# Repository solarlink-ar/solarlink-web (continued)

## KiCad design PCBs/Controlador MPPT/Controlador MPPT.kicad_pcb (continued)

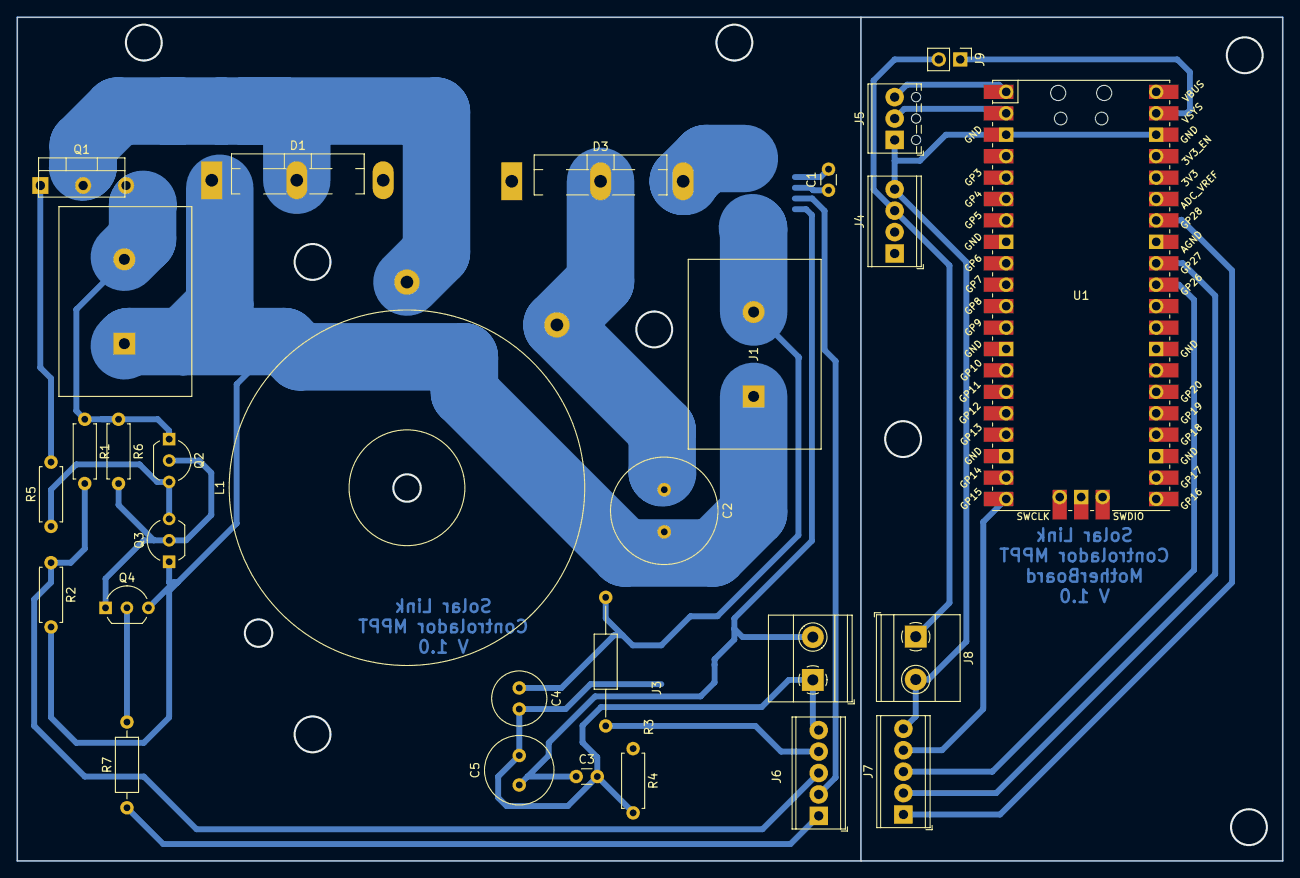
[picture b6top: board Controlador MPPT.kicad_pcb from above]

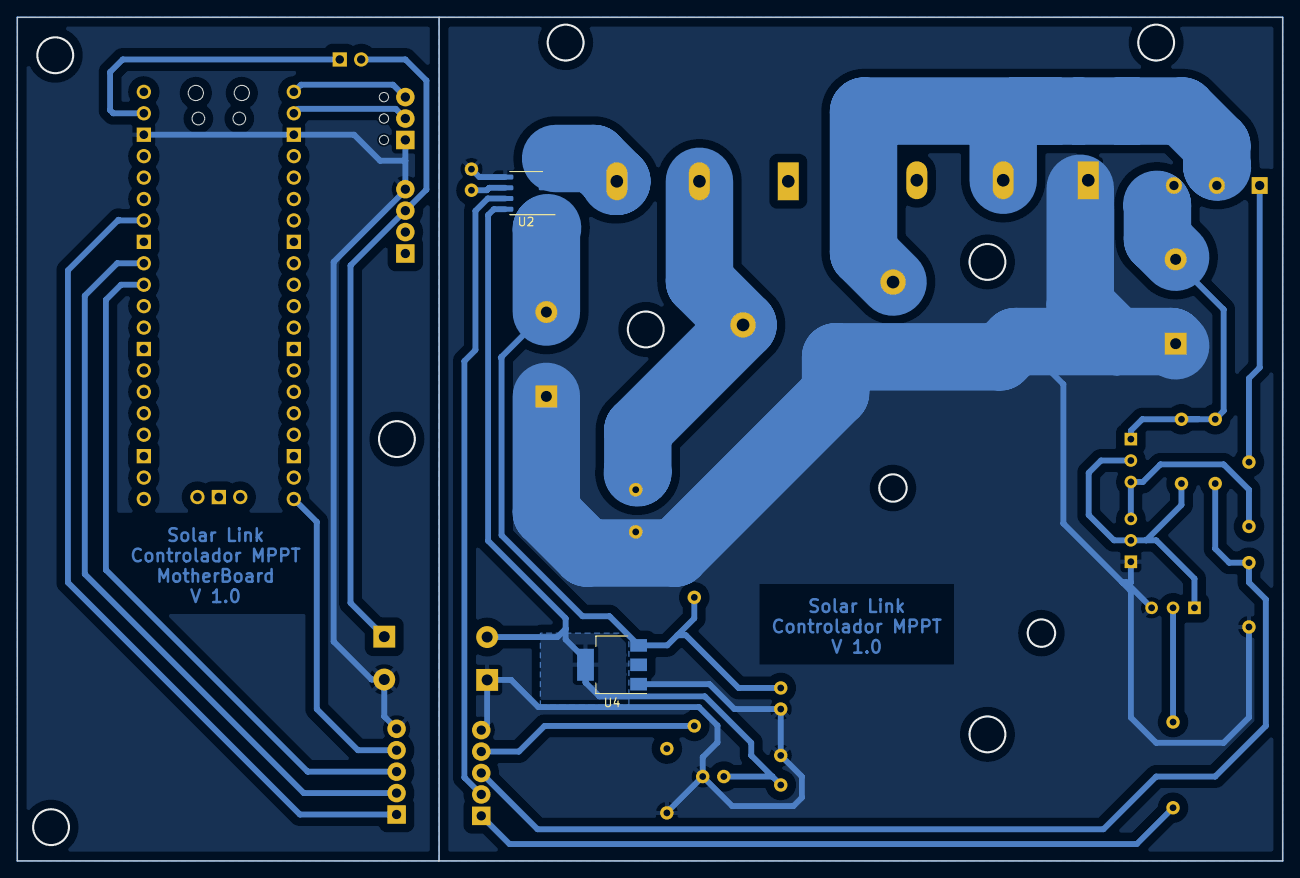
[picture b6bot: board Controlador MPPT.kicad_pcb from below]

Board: 2 copper layers, 150.0 x 100.0 mm, 31 parts (2 on the bottom side), 19 nets.

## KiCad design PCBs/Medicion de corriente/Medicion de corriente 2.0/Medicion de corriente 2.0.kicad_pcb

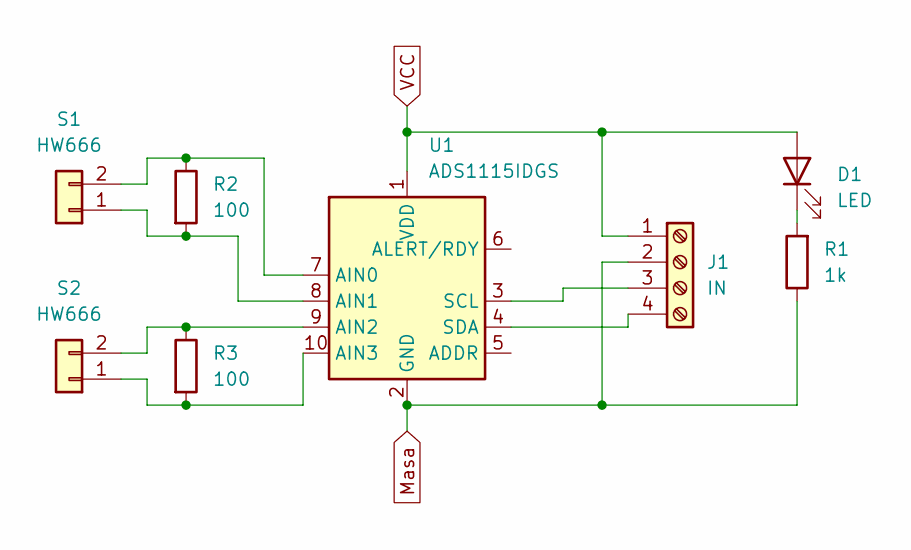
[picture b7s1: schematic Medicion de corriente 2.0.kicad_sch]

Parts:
D1: LED; LED_D3.0mm
J1: IN; TerminalBlock_Phoenix_MPT-0,5-4-2.54_1x04_P2.54mm_Horizontal
R1: 1k; R_Axial_DIN0207_L6.3mm_D2.5mm_P7.62mm_Horizontal
R2, R3: 100; R_Axial_DIN0207_L6.3mm_D2.5mm_P7.62mm_Horizontal
S1, S2: HW666; PinHeader_1x02_P2.54mm_Vertical
U1: ADS1115IDGS; PinHeader_1x10_P2.54mm_Vertical

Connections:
Masa: J1.2, R1.1, U1.2 (GND)
unnamed: D1.1 (K), R1.2
unnamed: J1.3, U1.3 (SCL)
unnamed: J1.4, U1.4 (SDA)
unnamed: R2.2, S1.1, U1.8 (AIN1)
unnamed: R2.1, S1.2, U1.7 (AIN0)
unnamed: R3.2, S2.1, U1.10 (AIN3)
unnamed: R3.1, S2.2, U1.9 (AIN2)
VCC: D1.2 (A), J1.1, U1.1 (VDD)

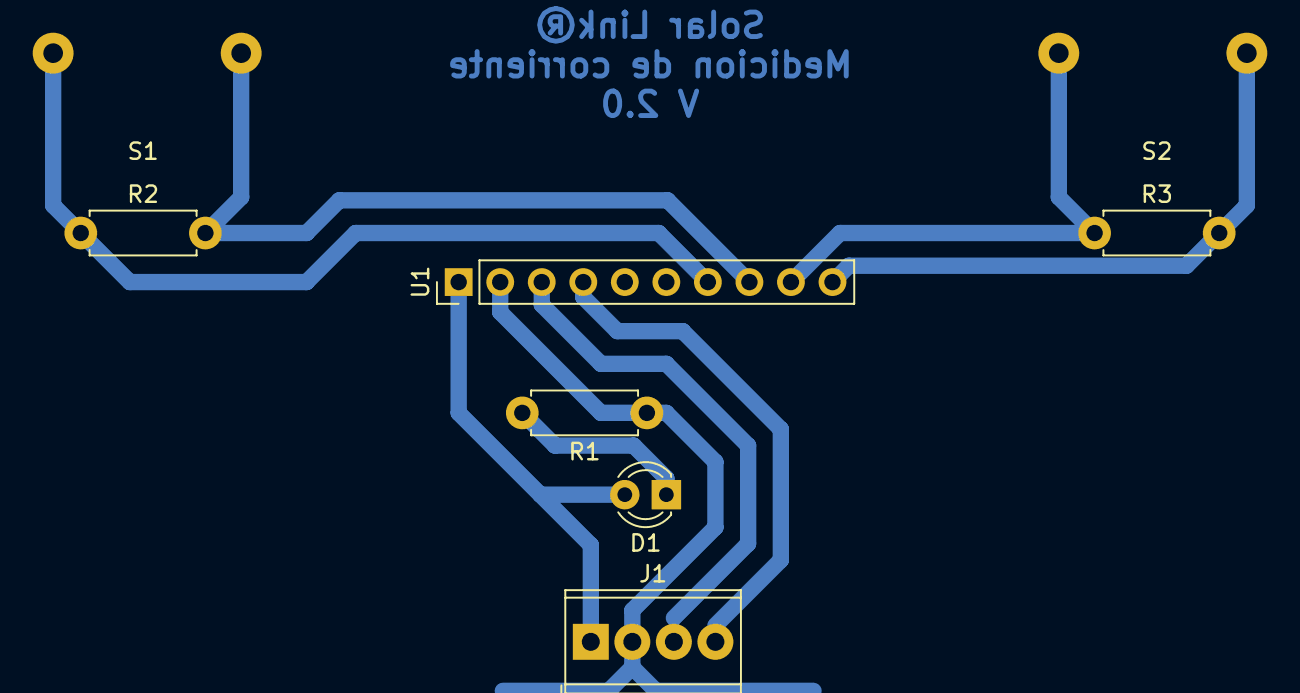
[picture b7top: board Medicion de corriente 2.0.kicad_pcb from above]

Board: 2 copper layers, 8 parts (0 on the bottom side), 9 nets.

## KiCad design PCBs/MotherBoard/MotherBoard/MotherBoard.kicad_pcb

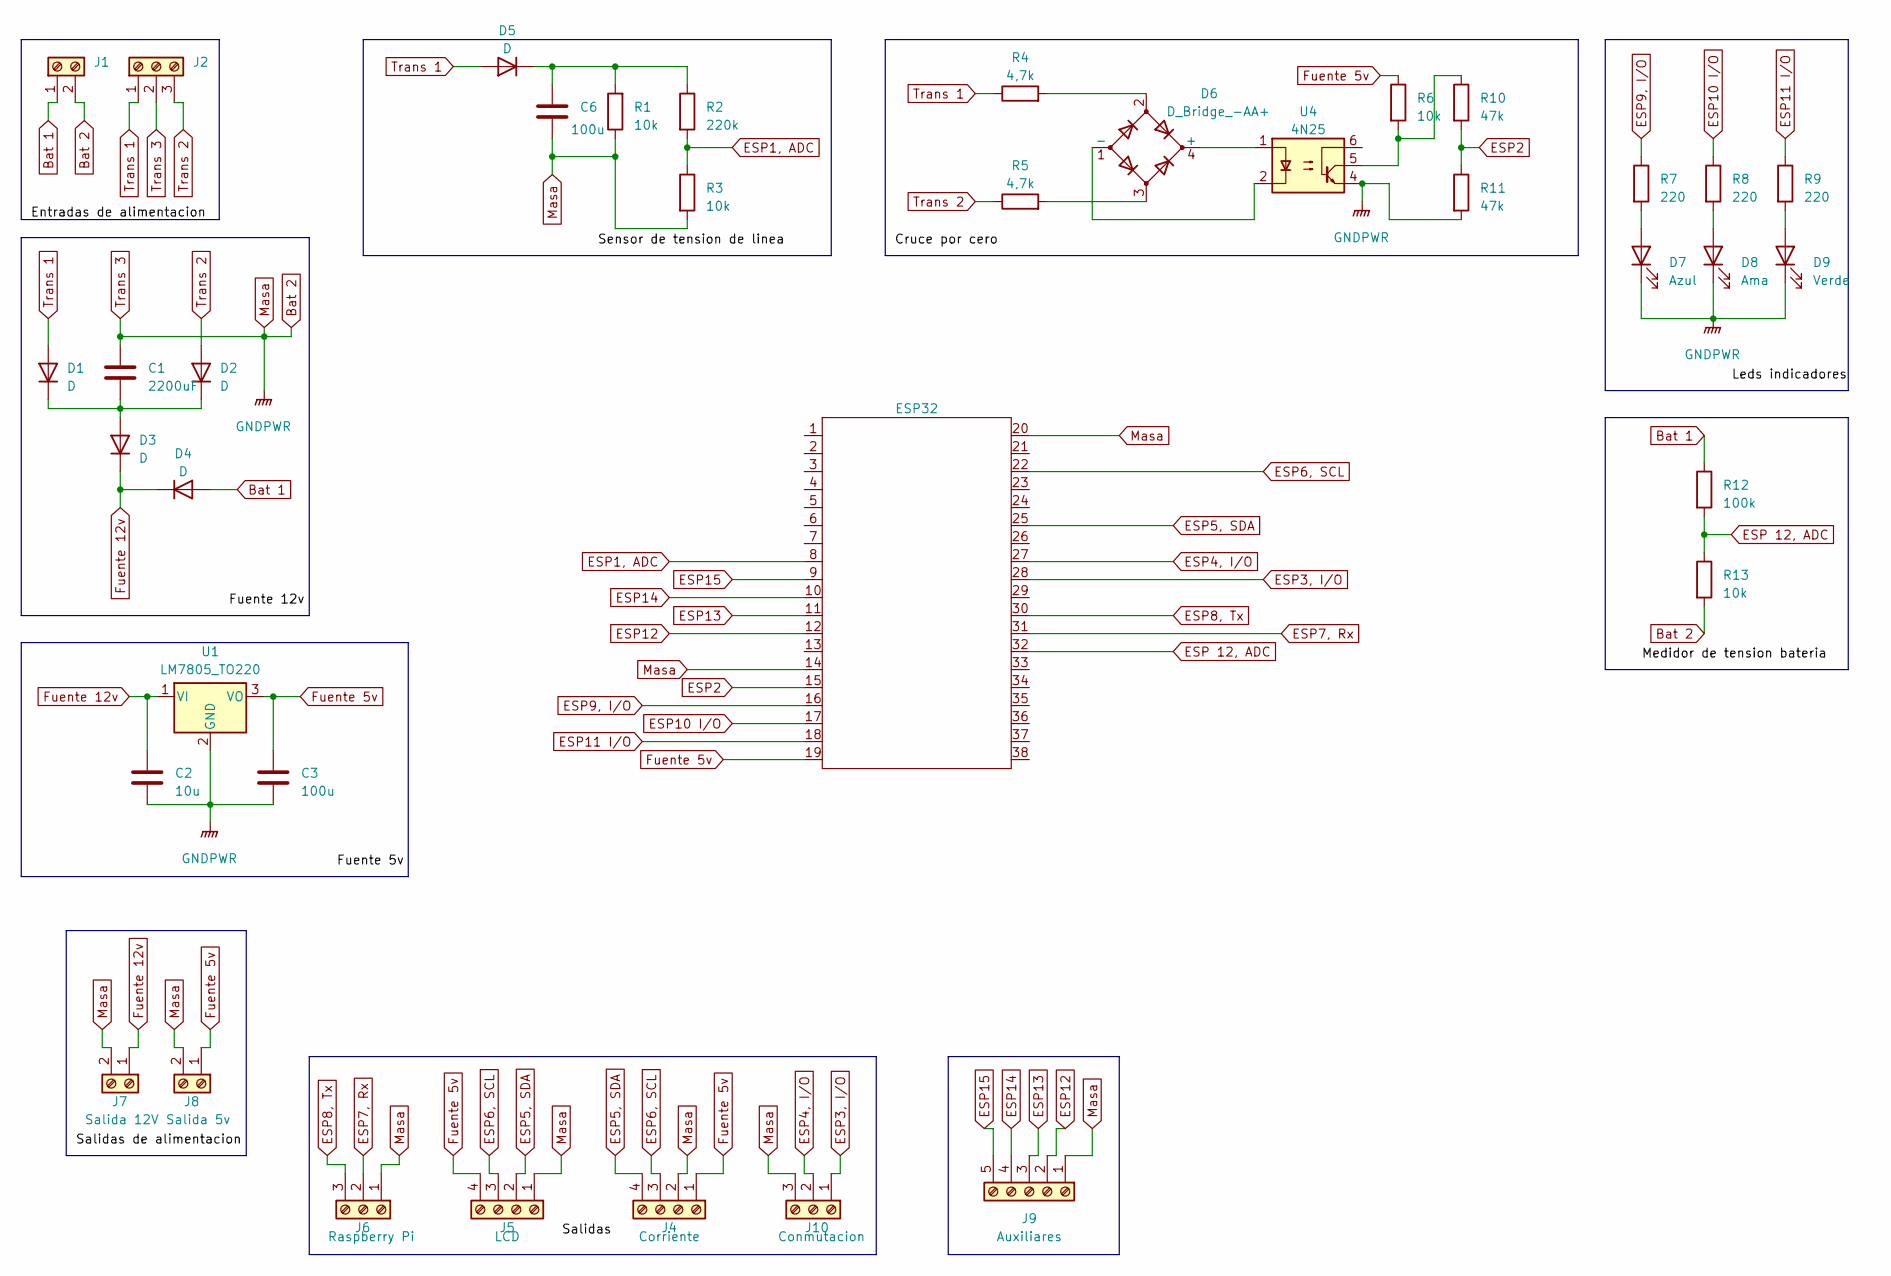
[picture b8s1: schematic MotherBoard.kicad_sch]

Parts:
C1: 2200uF; C_Radial_D16.0mm_H25.0mm_P7.50mm
C2: 10u; C_Radial_D6.3mm_H11.0mm_P2.50mm
C3, C6: 100u; C_Radial_D8.0mm_H11.5mm_P3.50mm
D1, D2, D3, D4, D5: D; D_DO-34_SOD68_P7.62mm_Horizontal
D6: D_Bridge_-AA+; Diode_Bridge_Round_D9.0mm
D7: Azul; LED_D3.0mm
D8: Ama; LED_D3.0mm
D9: Verde; LED_D3.0mm
ESP32: ESP32 NODEMCU
J1: Bateria; TerminalBlock_Phoenix_MKDS-1,5-2-5.08_1x02_P5.08mm_Horizont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
J2: Transformador; TerminalBlock_Phoenix_MKDS-1,5-3-5.08_1x03_P5.08mm_Horizont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
J4: Corriente; TerminalBlock_Phoenix_MPT-0,5-4-2.54_1x04_P2.54mm_Horizontal
J5: LCD; TerminalBlock_Phoenix_MPT-0,5-4-2.54_1x04_P2.54mm_Horizontal
J6: Raspberry Pi; TerminalBlock_Phoenix_MPT-0,5-3-2.54_1x03_P2.54mm_Horizontal
J7: Salida 12V; TerminalBlock_Phoenix_MKDS-1,5-2-5.08_1x02_P5.08mm_Horizont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
J8: Salida 5v; TerminalBlock_Phoenix_MKDS-1,5-2-5.08_1x02_P5.08mm_Horizont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
J9: Auxiliares; TerminalBlock_Phoenix_MPT-0,5-5-2.54_1x05_P2.54mm_Horizontal
J10: Conmutacion
R1, R3, R6, R13: 10k; R_Axial_DIN0207_L6.3mm_D2.5mm_P7.62mm_Horizontal
R2: 220k; R_Axial_DIN0204_L3.6mm_D1.6mm_P5.08mm_Horizontal
R4, R5: 4,7k; R_Axial_DIN0204_L3.6mm_D1.6mm_P5.08mm_Horizontal
R7, R8, R9: 220; R_Axial_DIN0207_L6.3mm_D2.5mm_P7.62mm_Horizontal
R10, R11: 47k; R_Axial_DIN0204_L3.6mm_D1.6mm_P5.08mm_Horizontal
R12: 100k; R_Axial_DIN0207_L6.3mm_D2.5mm_P7.62mm_Horizontal
U1: LM7805_TO220; TO-220-3_Vertical
U4: 4N25; DIP-6_W7.62mm

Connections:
Bat 1: D4.2 (A), J1.1, R12.1
Bat 2: C1.1, C2.2, C3.2, C6.2, D7.1 (K), D8.1 (K), D9.1 (K), ESP32.14 (GND), ESP32.20 (GND), J1.2, J2.2, J4.2, J5.1, J6.1, J7.2, J8.2, J9.1, J10.3, R1.1, R3.2, R11.2, R13.2, U1.2 (GND), U4.4; also elsewhere on the board
ESP1, ADC: ESP32.8 (ADC1_5,RTCGPIO8,GPIO33,TOUCH_8), R2.2, R3.1
ESP2: ESP32.15 (ADC2_4,RTCGPIO14,GPIO13,TOUCH_4,HSPI_MO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), R10.2, R11.1
ESP3, I/O: ESP32.28 (GPIO18,VSPI_CLK), J10.1; also elsewhere on the board
ESP4, I/O: ESP32.27 (GPIO19,VSPI_MISO), J10.2; also elsewhere on the board
ESP5, SDA: ESP32.25 (GPIO21,I2C_SDA), J4.4, J5.2
ESP6, SCL: ESP32.22 (GPIO22,I2C_SCL), J4.3, J5.3
ESP7, Rx: ESP32.31 (GPIO16,RX2), J6.2
ESP8, Tx: ESP32.30 (GPIO17,TX2), J6.3
ESP9, I/O: ESP32.16 (SHD/SD2,GPIO09), R7.1
ESP10 I/O: ESP32.17 (SWP/SD3,GPIO10), R8.1
ESP11 I/O: ESP32.18 (CSC/CMD,GPIO11), R9.1
ESP12: ESP32.12 (ADC2_6,RTCGPIO16,GPIO32,TOUCH_6,HSPI_CL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), J9.2
ESP13: ESP32.11 (ADC2_7,RTCGPIO17,GPIO27,TOUCH_7), J9.3
ESP14: ESP32.10 (ADC2_9,RTCGPIO7,GPIO26,DAC_2), J9.4
ESP15: ESP32.9 (ADC2_8,RTCGPIO8,GPIO25,DAC_1), J9.5
ESP 12, ADC: ESP32.32 (GPIO4,RTC_GPIO10,ADC2_0,TOUCH_0,SD_DAT1), R12.2, R13.1
Fuente 5v: C3.1, ESP32.19 (5v), J4.1, J5.4, J8.1, R6.1, U1.3 (VO)
Fuente 12v: C2.1, D3.1 (K), D4.1 (K), J7.1, U1.1 (VI)
unnamed: C1.2, D1.1 (K), D2.1 (K), D3.2 (A)
unnamed: C6.1, D5.1 (K), R1.2, R2.1
unnamed: D6.4 (+), U4.1
unnamed: D6.1 (-), U4.2
unnamed: D6.2, R4.2
unnamed: D6.3, R5.2
unnamed: D7.2 (A), R7.2
unnamed: D8.2 (A), R8.2
unnamed: D9.2 (A), R9.2
unnamed: R6.2, R10.1, U4.5
Trans 1: D1.2 (A), D5.2 (A), J2.1, R4.1
Trans 2: D2.2 (A), J2.3, R5.1

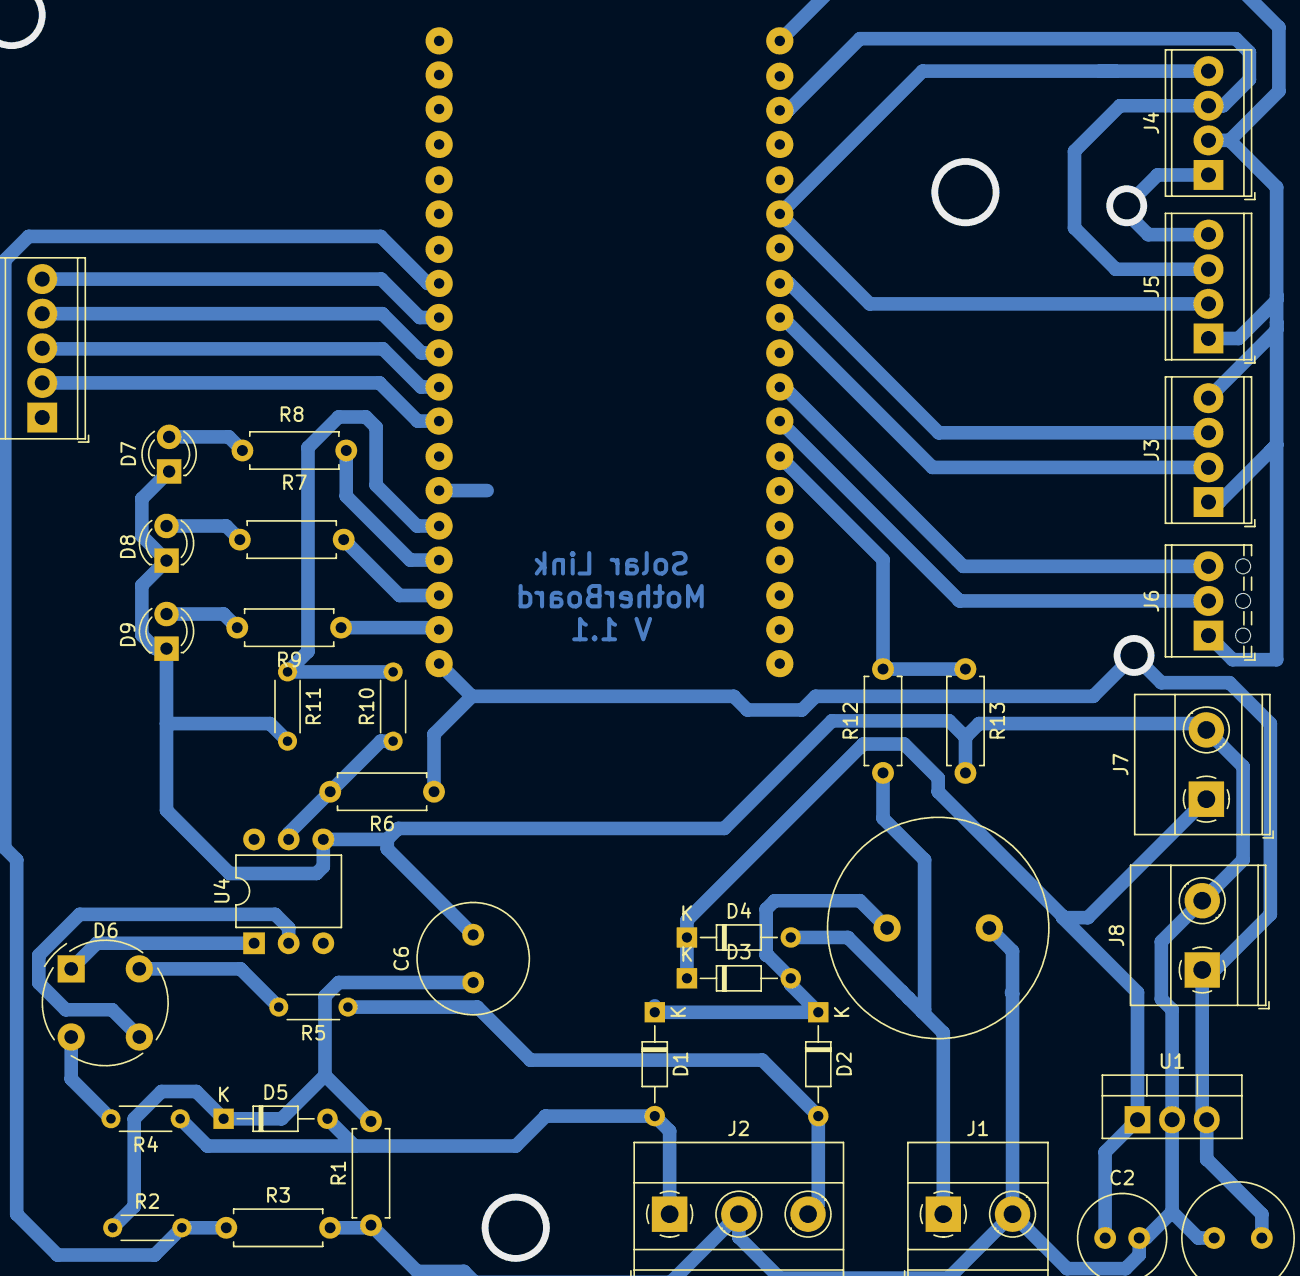
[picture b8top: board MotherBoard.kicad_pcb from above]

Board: 2 copper layers, 38 parts (0 on the bottom side), 32 nets.

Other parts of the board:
J3: Conmutacion; TerminalBlock_Phoenix_MPT-0,5-4-2.54_1x04_P2.54mm_Horizontal

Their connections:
Bat 2: J3.1, J3.4; also elsewhere on the board
ESP3, I/O: J3.2; also elsewhere on the board
ESP4, I/O: J3.3; also elsewhere on the board

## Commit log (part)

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2023-04-10 Añadir trabajo previo al git
2023-04-10 Test
2023-04-10 Revert "Test"
    This reverts commit 173dac9969698521e6f68043beea7c2eda802ff4.
2023-04-10 Another test
2023-04-10 y bueno
2023-04-10 Editar y arreglar bugs de diseño en el CSS
2023-04-21 Updated file name changes made last wednesday
2023-04-21 Changed container properties to fit the page. Added contact section skeleton pending further implementation.
2023-04-21 Containers are automatically centered when entering the webpage through a mobile device.
2023-04-21 UI updates to main page
2023-04-27 hola
2023-04-27 GUI changes
2023-04-28 Ported to django
2023-04-30 href ported to django
2023-05-03 Minor content updates.
2023-05-03 added get args support
2023-05-05 Minor CSS changes.
2023-05-05 Reorg working directory
2023-05-05 Even further graphical improvements
2023-05-06 project description
2023-05-06 Added micropython project files
2023-05-08 Added contact images
2023-05-08 WIP Gallery.
2023-05-10 correction of the project dates
2023-05-10 Finished page. Placeholder replacement pending.
2023-05-12 Replaced first batch of placeholders.
2023-05-15 added branch for solarlink web
2023-05-15 replaced gallery images
2023-05-15 Fixed datos def, partly fixed carousel.
2023-05-15 Replaced all placeholders.
2023-05-19 Added staging folder for uploading to the temp host
2023-05-22 minor changes
2023-05-22 added new database app
2023-05-22 Database prototype
2023-05-22 db corrected
2023-06-05 login first try
2023-06-05 add django default login template
2023-06-06 gitignore
2023-06-07 correct template problem
2023-06-07 Fixed contacto and galeria pages.
2023-06-07 add password confirmation
2023-06-07 configure gitignore
2023-06-08 correct html's next problem
2023-06-13 add login, product_id and data post test
2023-06-22 database
2023-06-26 test with 4x20 display
2023-07-11 calibracion de mediciones con el PCB
2023-07-15 merge
2023-07-15 Auto stash before merge of "solarlink_web" and "origin/solarlink_web"
2023-08-02 add two current lines support
2023-08-04 clean
2023-08-04 model update
2023-08-04 webapp template
    Archivos para trabajar
2023-08-05 add models, enhance login
2023-08-06 class support
2023-08-07 object update
2023-08-07 login bug corrected
2023-08-07 POO reorg
2023-08-09 venv config
2023-08-09 optimized static files' paths
2023-08-09 updated template.html dir & references
2023-08-09 template order corrected
2023-08-09 restored some images that were deleted by accident
2023-08-09 Revert "celery configuration"
    This reverts commit 6b64ba370be5d97619176674b9141c8bfa242920.
2023-08-09 main cleaned
2023-08-10 cron setup and register form
2023-08-10 Create main.c
    comienzos programa mppt
2023-08-11 actualizado .gitignore
2023-08-11 removed venv from the repo
2023-08-11 empezamos a traspasar el nuevo diseño
2023-08-12 Update main.c
    terminado logica basica
2023-08-16 cambios en header y footer
2023-08-16 new userpage, no content yet
2023-08-16 mi odio por django no conoce límites
2023-08-16 mi amor por django no conoce limites
2023-08-23 first try of database sorter system
2023-08-23 Arregle problema de imagenes, menu depslegable, porblema con body.
2023-08-23 Arreglando error de imagenes y traspasando viejo diseño de pagina web
2023-08-23 Agregando funcionalidad a botones interactivos (instagram, galeria, mail)
2023-08-28 Estandarice la pagina login
2023-08-28 django static configuration
2023-08-28 ignored __pycache__ folders
2023-08-28 further changes to the code skeleton for the commuter
2023-08-29 C > Python
2023-08-29 C no es lindo
2023-08-31 mppt lcd y sensores finalizado. Te amo C
2023-09-04 django-ized
2023-09-04 update db, finish db daily sorter, sorter test view
2023-09-04 main page
2023-09-04 vercel support
2023-09-04 vercel host allowed
2023-09-04 django-blog??
2023-09-04 white noise??
2023-09-04 settings path corrected
    NO CONFIAR EN TUTORIALES DE GOOGLE CHOTOS QUE NO EXPLICAN POR QUE HACEN LO QUE HACEN Y QUE CAMBIAR PARA TU PROYECTO
2023-09-04 staticfiles fix test
2023-09-04 whitenoise fix test
2023-09-05 investigando multithreading, código skeleton, WIP
2023-09-05 small fix
2023-09-05 secret key added and domain allowed
2023-09-05 unused directiories deleted
2023-09-05 static dirs and static root error corrected
2023-09-06 created a weblink class
2023-09-06 added skeleton methods for the weblink class
2023-09-06 Arreglé la galería y linkee perfiles de ig, linkedin y mail
2023-09-12 signup verification, db sorter, mail support
    mail sending support, signup verification with mail, celery and crontab support for db sorter task and mail sending task
2023-09-12 I love UART
2023-09-12 test, el conmutador funciona al recibir la señal. falta probar el cruce por cero
2023-09-12 UART nashe
2023-09-13 Termine el frontend de confirmacion de mail
2023-09-15 added complete measure method
2023-09-19 uart test finished, 10/10 wholesome chungus
2023-09-19 estructura basica
2023-10-02 Empece a hacer el forntend de la pagina de user managment
2023-10-02 Segui editando el frontend de la pagina de user managment
2023-10-02 uartbros we're so back
2023-10-02 grafico para ahorro inicio
2023-10-03 password reset logic
2023-10-03 varios cambios
2023-10-04 form convertion, password reset system completed, auto token delete done
    todas las vistas de auth (login, registro, etc) se convirtieron en forms de django. El sistema de password reset está completado. El sistema que borra los token cada 2hs se ha terminado e incluido co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
2023-10-04 Seccion ahorro mejorada, cambio de libreria para graficos y mas graficos
2023-10-05 API login
2023-10-06 cambios generales app
2023-10-06 me falla gitkraken aaa
2023-10-08 primer test tablero
2023-10-08 DB sorter 2.0
    de 120 a 60 lineas de codigo!!
2023-10-08 comments
2023-10-09 arreglo css de galeria
2023-10-09 Arregle parte del css de la galeria
2023-10-09 Me agregue a los integrantes
2023-10-09 test conmutacion con tablero
2023-10-09 Empece con el frontend de el apartado de registro
2023-10-09 django template format para signup
2023-10-10 logica conmutacion
2023-10-10 Mail - confirmacion usuario
    To backend -
    variables{
    url;
    mail
    };
2023-10-11 Avancé con la pagina de user mngmnt
2023-10-11 Mas cambios en la pagina de user mngmnt
2023-10-11 Trabaje con la galería
2023-10-11 error fixing
2023-10-11 footer corrections
2023-10-11 Beginning verious html templates for specific usage
2023-10-11 comenzo edesur API
2023-10-11 update base de datos con lineas, static reorg
2023-10-12 bs4 added to requirements
2023-10-12 cambios muy menores
2023-10-12 load data view
2023-10-12 cambiando cositas!
2023-10-12 standarization
2023-10-12 Minor fixes
2023-10-13 django-ization, subprocess con el worker de celery
2023-10-13 More frontend adjustments
2023-10-14 data index v1 final si dios quiere (no va a querer)
2023-10-15 minor changes pero nashes
2023-10-17 responsive templates, login especific for OS
2023-10-17 login form template
2023-10-17 new login template, django-ized
2023-10-17 New login and register templates, really hard work. ALL AGAIN
2023-10-18 ASGI support with daphne
2023-10-18 Templates all done! (almost, djangification pending)
2023-10-18 logica conmutacion terminada int por cruce por cero
2023-10-19 djangoization user_mngmnt templates
2023-10-19 Cambie las fotos a unas de menor calidad asi carga todo más rápido
2023-10-19 fixes on login and register
2023-10-19 cruce por cero andando
2023-10-19 setup for second deploy, mail html's fix
2023-10-20 django compressor removed (read only server) master css fix
2023-10-20 ASGI
2023-10-20 WSGI
2023-10-20 test2
2023-10-20 test3
2023-10-20 test 4
2023-10-20 test4
2023-10-20 celery, crontab and sqlite not supported by vercel adaptation to postgresql, celery to views
2023-10-20 requirements update postgree and dotenv support
2023-10-20 Squashed commit of the following:
    commit 0894f7cfb157294b4a62506a1cd863207a21134d
    Author: IvanCenyko <ivanchicago70@gmail.com>
    Date: Fri Oct 20 09:54:02 2023 -0300
    requirements update
    postgree and dotenv support
    commit 549475abf5696bf5700f032c75bcd1a7245c99b4
2023-10-20 ASGI test
2023-10-20 Squashed commit of the following:
    commit 9718f941acb600c440b4f3d737d35f2a6738848c
    Author: IvanCenyko <ivanchicago70@gmail.com>
    Date: Fri Oct 20 13:33:18 2023 -0300
    vercel cron jobs with views
    commit 0894f7cfb157294b4a62506a1cd863207a21134d
    Author: IvanCenyko <ivanchicago70@gmail.com>
2023-10-20 cron jobs with django views
2023-10-20 DEPLOY TEST
2023-10-20 cambios en la galería
2023-10-20 CRON TEST
2023-10-20 Cron disabled
2023-10-20 minor mail changes
2023-10-20 update en galería
2023-10-21 Cambios grandes en la galería
2023-10-21 async support for apilogin view
2023-10-21 async support for api login view
2023-10-22 galería termina por fin mas o menos
    Faltan las flechas q no se xq no me las toma
2023-10-23 APILogin support for json and data POST keywords
2023-10-23 GALERÍA COOL TERMINADA
2023-10-23 APILogin support for json and data POST keywords
    (cherry picked from commit b7208eefc927eb23e74667f9523906398f5a488f)
2023-10-23 se comenzó el cálculo de datos de usuario
2023-10-23 microdot terminado
2023-10-23 minor about us changes (minions added)
2023-10-23 moved upython files around
2023-10-23 i2c error corregido trigger de conmutacion reducido a 400W periodo del timer reducido a 100ms inicio de pruebas con RTC
2023-10-24 Online User Update (JS)
2023-10-24 SetOnlineUser test with js, db and backend
2023-10-24 Minor changes index
2023-10-24 More minor changes in graphs
2023-10-24 dia graph, online view, load data, should post
2023-10-24 Update microdot test file
2023-10-24 updated microdot once again. NOTE: use micropython 1.20.0
2023-10-25 Making 'datos actuales' actually work
2023-10-25 Fixes for stuff
2023-10-25 real time update, hour update
2023-10-25 logic irq handler error
2023-10-25 tiempo real delete when closing tab
2023-10-26 load data now update
2023-10-31 oniet tests
2023-11-06 database update, filter by timezone
2023-11-07 Cleaned branch
2023-11-07 versiones del main para post y no post
2023-11-07 Parte transmisor del sistema de posteo de datos
2023-11-07 Posteo de datos. Falta testeo.
2023-11-08 timezone settings fixed for database filter
2023-11-10 post thread main
2023-11-11 Iván Cenyko was here
2023-11-11 data filter for graphs
2023-11-12 Several minor stuff
2023-11-17 Squashed commit of the following:
    commit 207cc10c67e4768a11bde2e46933d034321dd6e0
    Author: Iván Cenyko <80519646+IvanCenyko@users.noreply.github.com>
    Date: Thu Nov 16 21:41:54 2023 -0300
    Update urls.py
    commit 14e22305189e1eb7acae6a6d7f0f18a5951b40df
    Author: IvanCenyko <ivanchicago70@gmail.com>
2023-11-17 debug false
2023-11-17 static
2023-11-17 index datos actuales fixed
2023-11-21 index datos actuales fixed
    (cherry picked from commit dff7d09e12d13fa0809e423763d22ce1daea4f66)
2023-11-21 directory reorganization
2023-11-21 Revert "Update README.md"
    This reverts commit 290ddd59fbbcf0af2d84b532df53864938999f02.
2023-11-23 Carpeta tecnica (primer commit jijiji)
2023-11-23 Carpeta tecnica sin codigos
2023-11-23 Carpeta de campo
2023-11-23 Proambiente
2023-11-23 Carpeta de campo código latex
2023-11-23 Proambiente código latex
2023-11-23 Archivo de KiCad regulador de tension
2023-11-23 Archivos de KiCad de plaquetas de medicion de corriente (1.0 y 2.0)
2023-11-23 MotherBoard 1.0, 2.0, y 3.0 archivos KiCad
2023-11-23 Cargador MPPT archivo KiCad
2023-11-23 TODOS los diseños 3D DEL PROYECTO (INCREIBLE) (SERGIO NO ESTOY ROBANDO CON COMMITS)
2023-11-23 Presentacion de Canva de Solar Link
2023-11-23 Archivos de word de los pedidos para mi amiga personal jaqueline
2023-11-23 PERDON ESTO NO IBA ACA
2023-11-23 Fotos para el readme
2023-11-24 actualizacion imagenes del readme
2023-11-24 readme fachero
2023-11-24 mas chico el logo!!
2023-11-24 cambios en las imagenes del readme
2023-11-24 banner añadido
2023-11-24 Foto con banner y remeras solar link
2024-04-03 Actualizacion de pines
    Se viene el MPPT 2.0, mas moderno, mas compacto, y mas practico
